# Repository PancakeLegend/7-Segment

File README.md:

# 7-Segment
 Modular 7-Segment Display

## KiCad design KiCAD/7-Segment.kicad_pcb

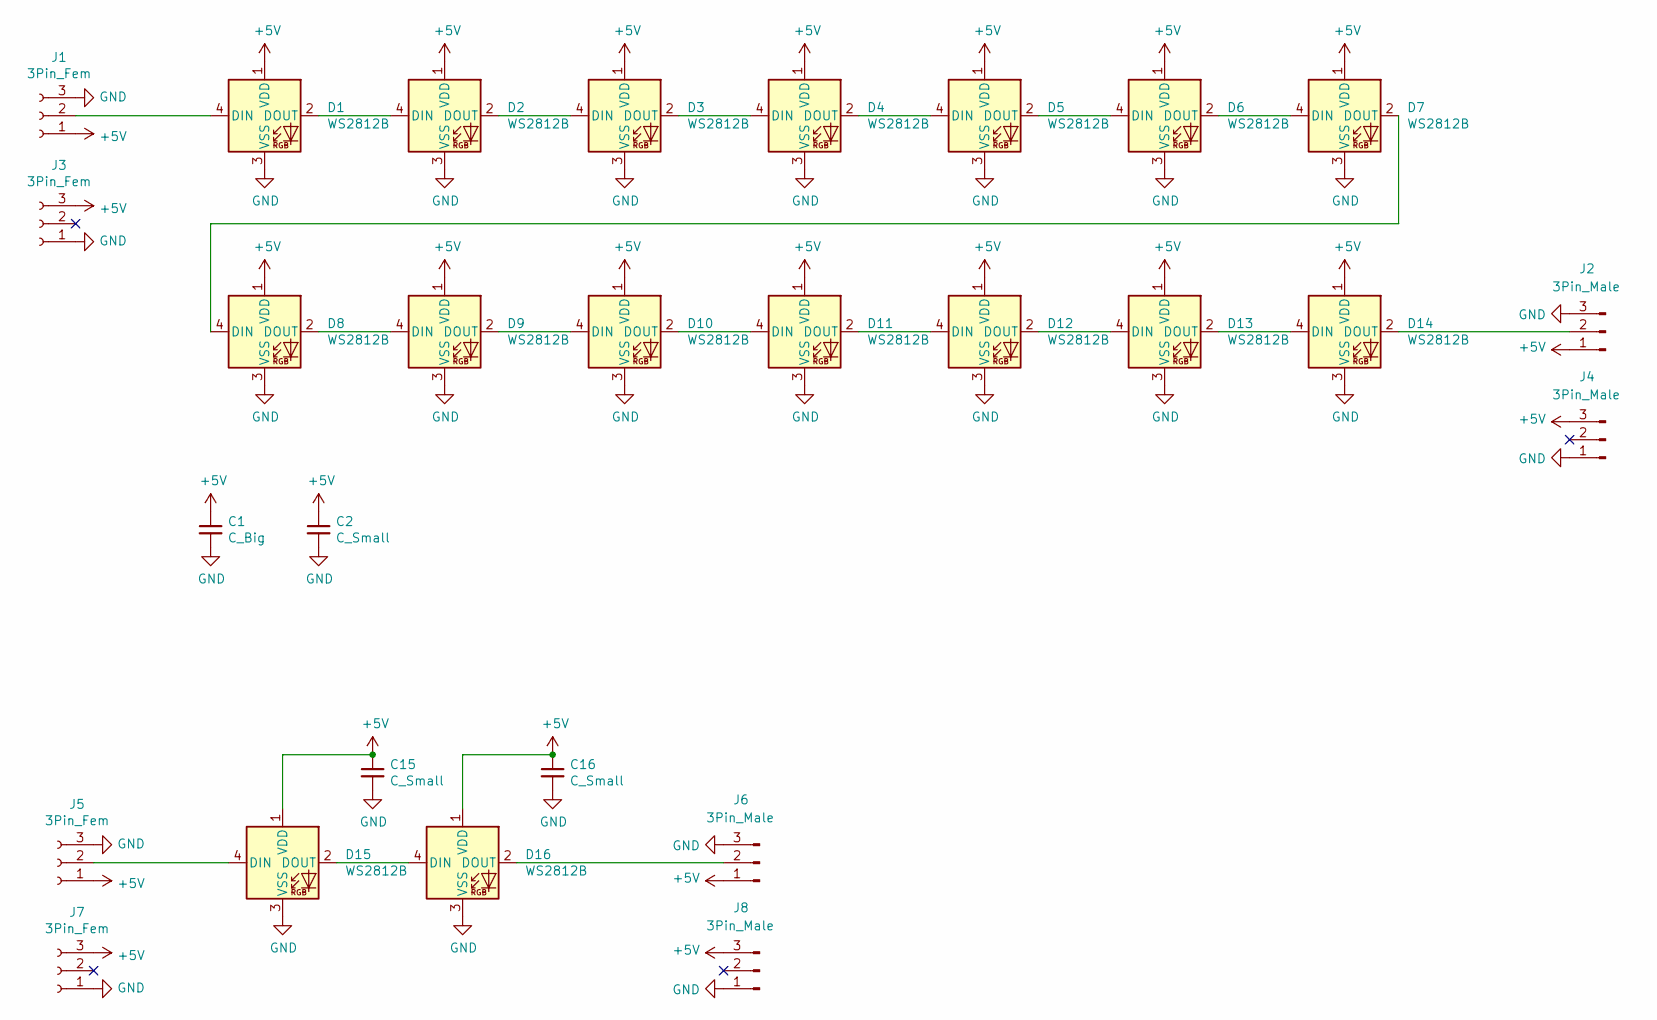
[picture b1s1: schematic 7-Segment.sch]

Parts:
C1: C_Big; CP_Elec_5x5.3
C2, C15, C16: C_Small; C_1206
D1, D2, D3, D4, D5, D6, D7, D8, D9, D10, D11, D12, D13, D14, D15, D16: WS2812B; LED_WS2812B-PLCC4
J1, J3, J5, J7: 3Pin_Fem; Header3Pin_04
J2, J4, J6, J8: 3Pin_Male; Header3Pin_04

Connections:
+5V: C1.1, C2.1, C15.1, C16.1, D1.1 (VDD), D2.1 (VDD), D3.1 (VDD), D4.1 (VDD), D5.1 (VDD), D6.1 (VDD), D7.1 (VDD), D8.1 (VDD), D9.1 (VDD), D10.1 (VDD), D11.1 (VDD), D12.1 (VDD), D13.1 (VDD), D14.1 (VDD), D15.1 (VDD), D16.1 (VDD), J1.1, J2.1, J3.3, J4.3, J5.1, J6.1, J7.3, J8.3
GND: C1.2, C2.2, C15.2, C16.2, D1.3 (VSS), D2.3 (VSS), D3.3 (VSS), D4.3 (VSS), D5.3 (VSS), D6.3 (VSS), D7.3 (VSS), D8.3 (VSS), D9.3 (VSS), D10.3 (VSS), D11.3 (VSS), D12.3 (VSS), D13.3 (VSS), D14.3 (VSS), D15.3 (VSS), D16.3 (VSS), J1.3, J2.3, J3.1, J4.1, J5.3, J6.3, J7.1, J8.1
unnamed: D1.2 (DOUT), D2.4 (DIN)
unnamed: D1.4 (DIN), J1.2
unnamed: D2.2 (DOUT), D3.4 (DIN)
unnamed: D3.2 (DOUT), D4.4 (DIN)
unnamed: D4.2 (DOUT), D5.4 (DIN)
unnamed: D5.2 (DOUT), D6.4 (DIN)
unnamed: D6.2 (DOUT), D7.4 (DIN)
unnamed: D7.2 (DOUT), D8.4 (DIN)
unnamed: D8.2 (DOUT), D9.4 (DIN)
unnamed: D10.2 (DOUT), D11.4 (DIN)
unnamed: D9.2 (DOUT), D10.4 (DIN)
unnamed: D11.2 (DOUT), D12.4 (DIN)
unnamed: D12.2 (DOUT), D13.4 (DIN)
unnamed: D13.2 (DOUT), D14.4 (DIN)
unnamed: D14.2 (DOUT), J2.2
unnamed: D15.2 (DOUT), D16.4 (DIN)
unnamed: D15.4 (DIN), J5.2
unnamed: D16.2 (DOUT), J6.2

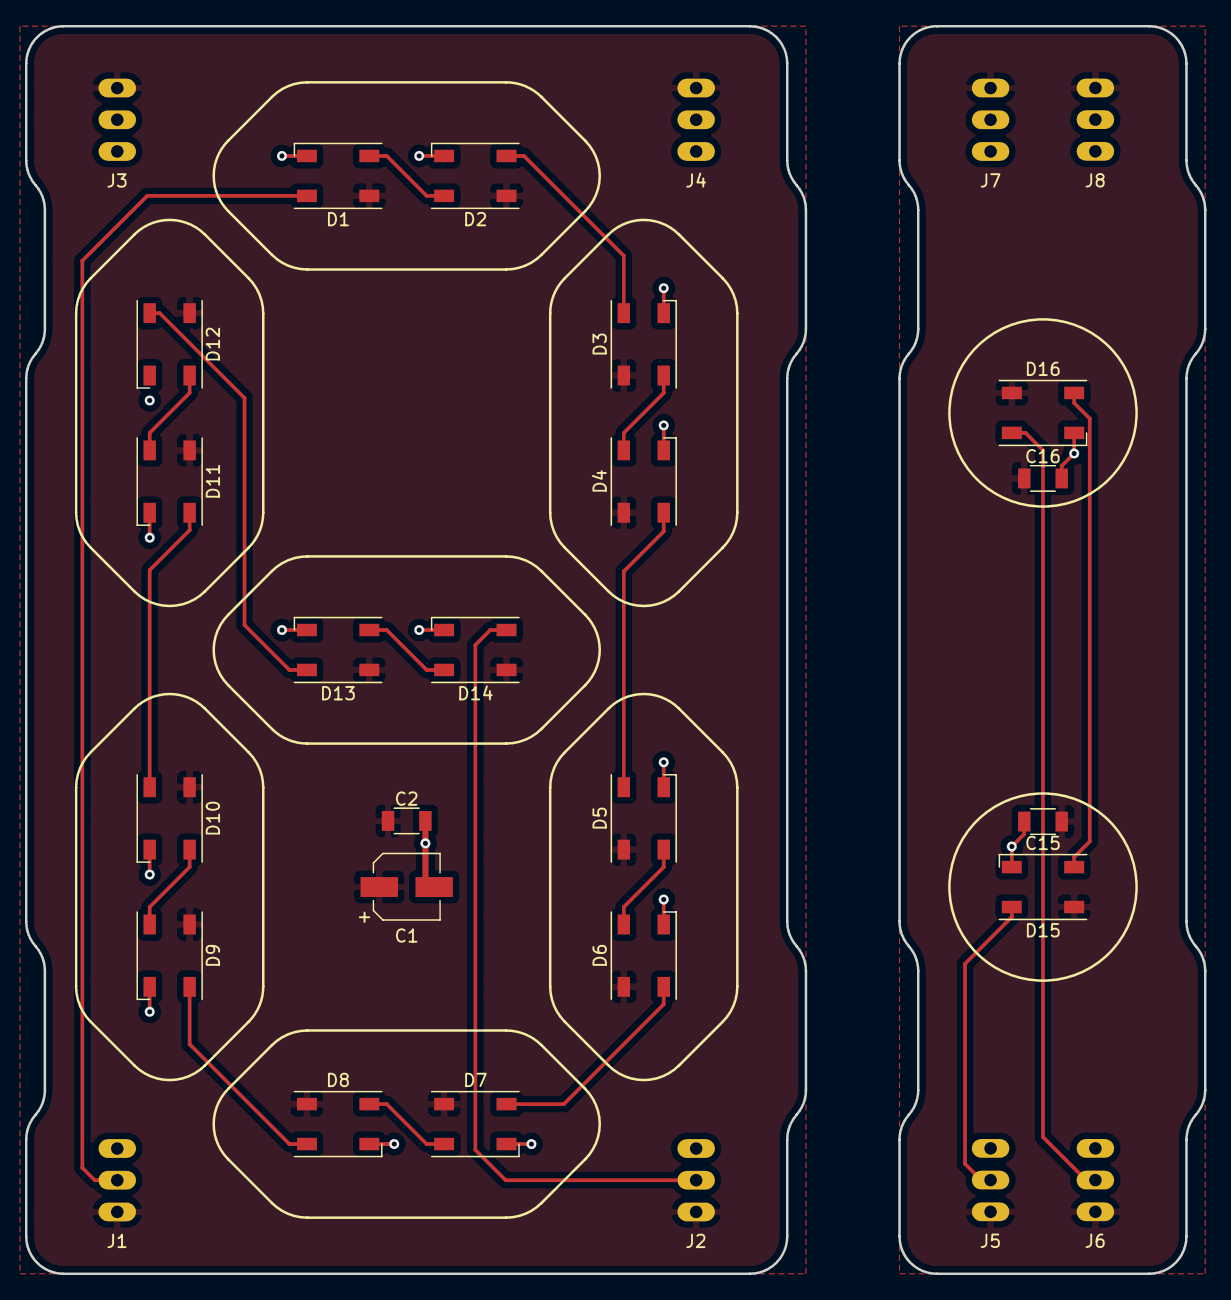
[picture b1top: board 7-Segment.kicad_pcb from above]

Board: 2 copper layers, 94.5 x 100.0 mm, 28 parts (0 on the bottom side), 20 nets.

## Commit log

2020-03-11 Initial Upload
2020-03-11 Re-organising folders
2020-03-14 Update 7-Segment.kicad_pcb
    Moved placeholder mount holes to Dwgs.User layer.
2020-03-19 2-LED per segment
    Changed from 1 to 2 LEDs per segment. Removed caps per LED and included 2 placeholder caps for the module.
2020-10-04 Iterative updates
